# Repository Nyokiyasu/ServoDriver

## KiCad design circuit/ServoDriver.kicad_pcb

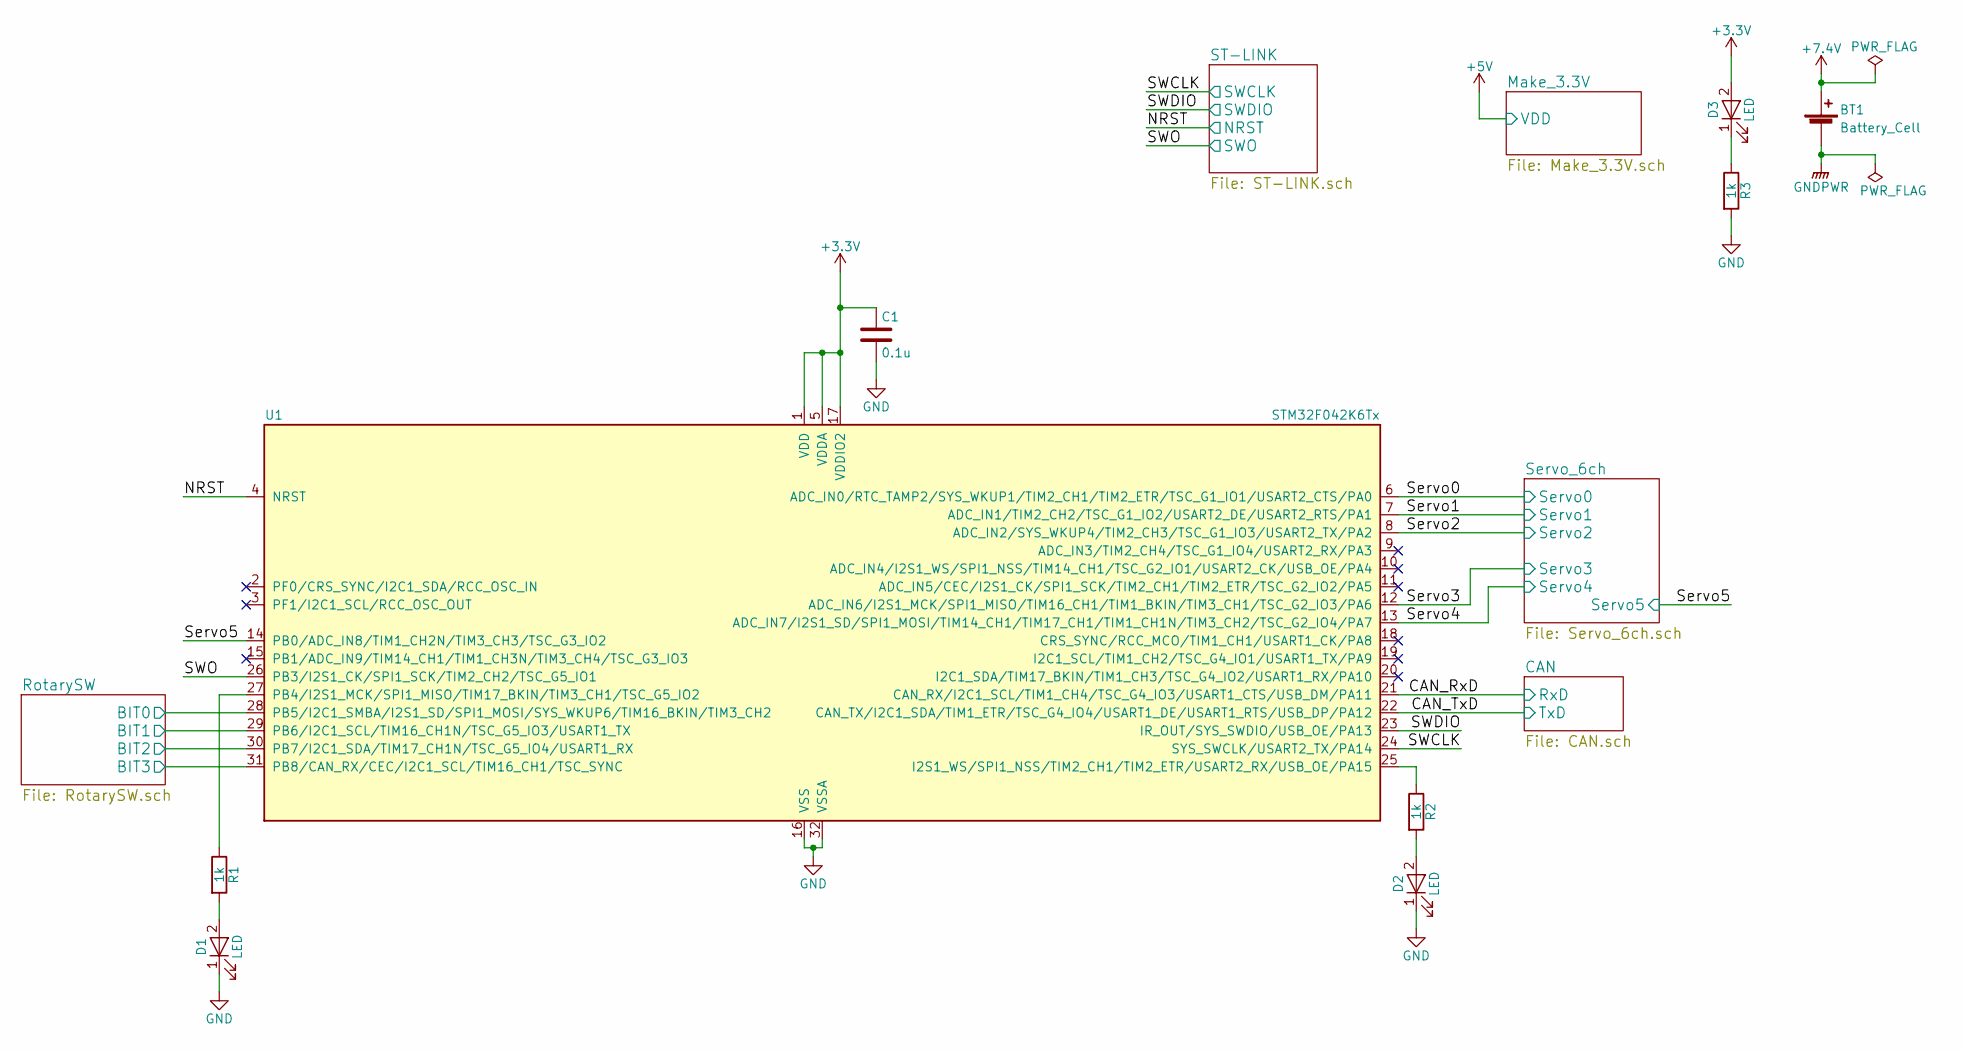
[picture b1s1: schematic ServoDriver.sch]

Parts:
BT1: Battery_Cell; XT_Mdot
C1: 0.1u; C_0603_HandSoldering
D1, D2, D3: LED; LED_D5.0mm
R1, R2, R3: 1k; R_0603_HandSoldering_LP
U1: STM32F042K6Tx; TQFP-32_7x7mm_Pitch0.8mm

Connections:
+3V3: C1.1, D3.2 (A), U1.1 (VDD), U1.5 (VDDA), U1.17 (VDDIO2); also elsewhere on the board
+7.4V: BT1.1 (+); also elsewhere on the board
/CAN_RxD: U1.21 (CAN_RX/I2C1_SCL/TIM1_CH4/TSC_G4_IO3/USA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); also elsewhere on the board
/CAN_TxD: U1.22 (CAN_TX/I2C1_SDA/TIM1_ETR/TSC_G4_IO4/USA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); also elsewhere on the board
/NRST: U1.4 (NRST); also elsewhere on the board
/RotarySW/BIT0: U1.28 (PB5/I2C1_SMBA/I2S1_SD/SPI1_MOSI/SYS_WKU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); also elsewhere on the board
/RotarySW/BIT1: U1.29 (PB6/I2C1_SCL/TIM16_CH1N/TSC_G5_IO3/USAR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); also elsewhere on the board
/RotarySW/BIT2: U1.30 (PB7/I2C1_SDA/TIM17_CH1N/TSC_G5_IO4/USAR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); also elsewhere on the board
/RotarySW/BIT3: U1.31 (PB8/CAN_RX/CEC/I2C1_SCL/TIM16_CH1/TSC_S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); also elsewhere on the board
/SWCLK: U1.24 (SYS_SWCLK/USART2_TX/PA14); also elsewhere on the board
/SWDIO: U1.23 (IR_OUT/SYS_SWDIO/USB_OE/PA13); also elsewhere on the board
/SWO: U1.26 (PB3/I2S1_CK/SPI1_SCK/TIM2_CH2/TSC_G5_IO1); also elsewhere on the board
/Servo0: U1.6 (ADC_IN0/RTC_TAMP2/SYS_WKUP1/TIM2_CH1/TI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); also elsewhere on the board
/Servo1: U1.7 (ADC_IN1/TIM2_CH2/TSC_G1_IO2/USART2_DE/U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); also elsewhere on the board
/Servo2: U1.8 (ADC_IN2/SYS_WKUP4/TIM2_CH3/TSC_G1_IO3/U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); also elsewhere on the board
/Servo3: U1.12 (ADC_IN6/I2S1_MCK/SPI1_MISO/TIM16_CH1/TI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); also elsewhere on the board
/Servo4: U1.13 (ADC_IN7/I2S1_SD/SPI1_MOSI/TIM14_CH1/TIM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); also elsewhere on the board
/Servo5: U1.14 (PB0/ADC_IN8/TIM1_CH2N/TIM3_CH3/TSC_G3_I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); also elsewhere on the board
GND: C1.2, D1.1 (K), D2.1 (K), R3.2, U1.16 (VSS), U1.32 (VSSA); also elsewhere on the board
GNDPWR: BT1.2 (-); also elsewhere on the board
unnamed: D1.2 (A), R1.2
unnamed: D2.2 (A), R2.2
unnamed: D3.1 (K), R3.1
unnamed: R1.1, U1.27 (PB4/I2S1_MCK/SPI1_MISO/TIM17_BKIN/TIM3_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)
unnamed: R2.1, U1.25 (I2S1_WS/SPI1_NSS/TIM2_CH1/TIM2_ETR/USAR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)

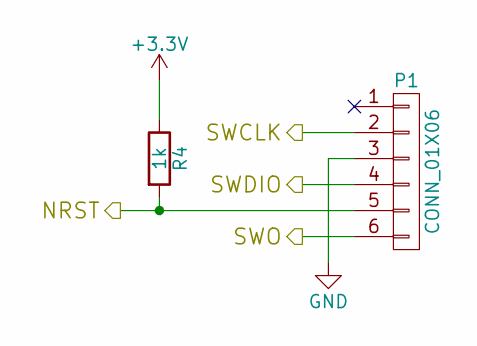
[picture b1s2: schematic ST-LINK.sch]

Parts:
P1: CONN_01X06; Pin_Header_Straight_1x06_Pitch2.54mm
R4: 1k; R_0603_HandSoldering

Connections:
+3V3: R4.1; also elsewhere on the board
/NRST: P1.5, R4.2; also elsewhere on the board
/SWCLK: P1.2; also elsewhere on the board
/SWDIO: P1.4; also elsewhere on the board
/SWO: P1.6; also elsewhere on the board
GND: P1.3; also elsewhere on the board

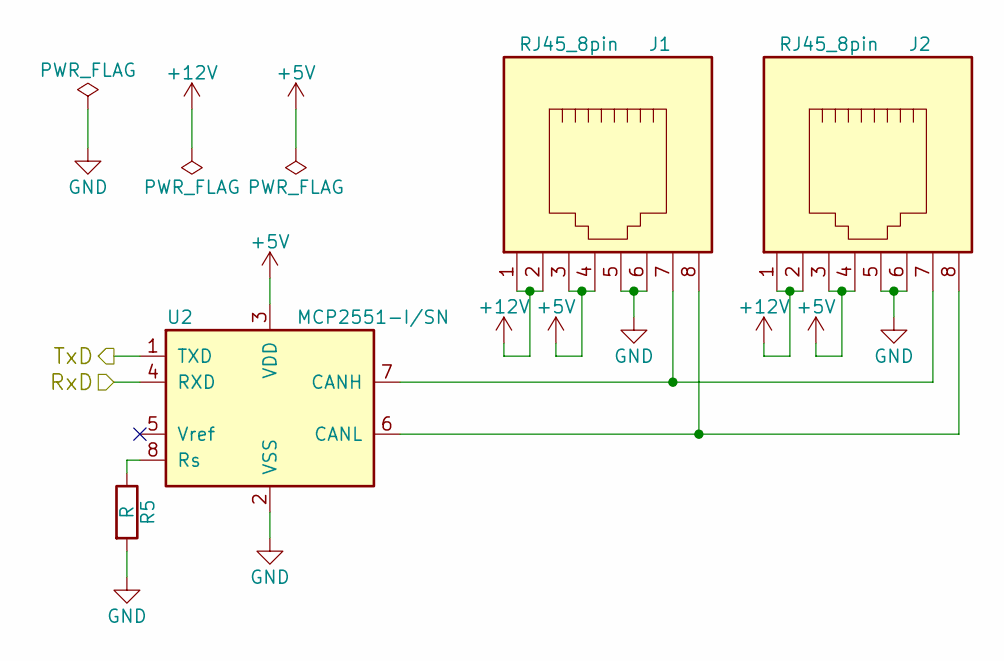
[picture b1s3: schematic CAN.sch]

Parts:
J1, J2: RJ45_8pin; 7810-8P8C
R5: R; R_0603_HandSoldering_LP
U2: MCP2551-I/SN; DIP-8_W7.62mm_Socket_LongPads

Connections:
+5V: J1.3, J1.4, J2.3, J2.4, U2.3 (VDD); also elsewhere on the board
+12V: J1.1, J1.2, J2.1, J2.2
/CAN_RxD: U2.4 (RXD); also elsewhere on the board
/CAN_TxD: U2.1 (TXD); also elsewhere on the board
GND: J1.5, J1.6, J2.5, J2.6, R5.2, U2.2 (VSS); also elsewhere on the board
unnamed: J1.7, J2.7, U2.7 (CANH)
unnamed: J1.8, J2.8, U2.6 (CANL)
unnamed: R5.1, U2.8 (Rs)

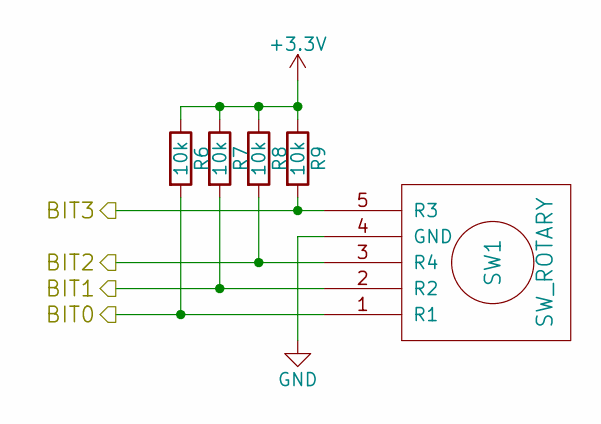
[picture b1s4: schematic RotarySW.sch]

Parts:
R6, R7, R8: 10k; R_0603_HandSoldering_LP
R9: 10k; R_Axial_DIN0207_L6.3mm_D2.5mm_P7.62mm_Horizontal
SW1: SW_ROTARY; RotarySW

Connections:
+3V3: R6.1, R7.1, R8.1, R9.1; also elsewhere on the board
/RotarySW/BIT0: R6.2, SW1.1 (R1); also elsewhere on the board
/RotarySW/BIT1: R7.2, SW1.2 (R2); also elsewhere on the board
/RotarySW/BIT2: R8.2, SW1.3 (R4); also elsewhere on the board
/RotarySW/BIT3: R9.2, SW1.5 (R3); also elsewhere on the board
GND: SW1.4 (GND); also elsewhere on the board

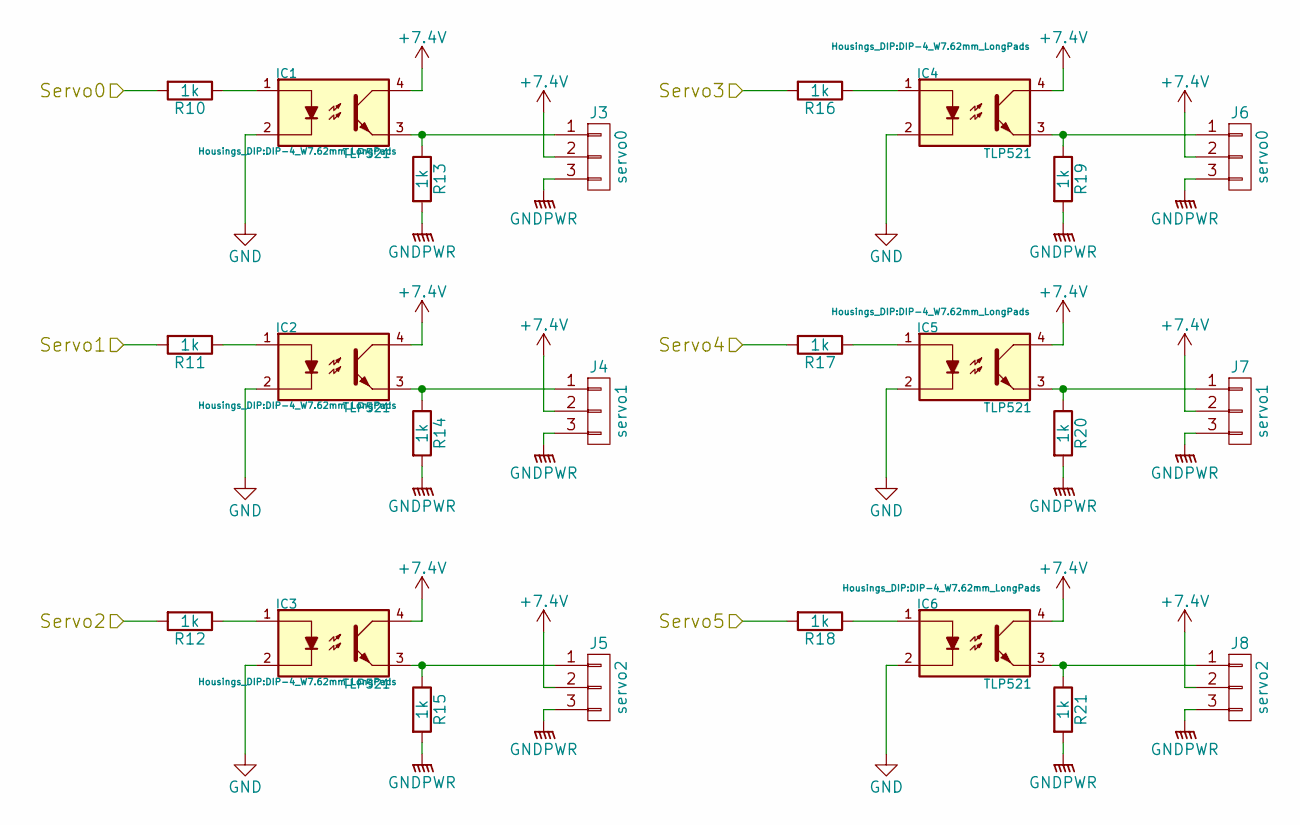
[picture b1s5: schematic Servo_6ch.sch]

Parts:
IC1, IC2, IC3, IC4, IC5, IC6: TLP521; DIP-4_W7.62mm_LongPads
J3, J6: servo0; XA_3Pin_LP
J4, J7: servo1; XA_3Pin_LP
J5, J8: servo2; XA_3Pin_LP
R10, R11, R12, R16, R17, R18: 1k; R_0603_HandSoldering
R13, R14, R15, R19, R20, R21: 1k; R_Axial_DIN0207_L6.3mm_D2.5mm_P7.62mm_Horizontal

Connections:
+7.4V: IC1.4, IC2.4, IC3.4, IC4.4, IC5.4, IC6.4, J3.2, J4.2, J5.2, J6.2, J7.2, J8.2; also elsewhere on the board
/Servo0: R10.2; also elsewhere on the board
/Servo1: R11.2; also elsewhere on the board
/Servo2: R12.2; also elsewhere on the board
/Servo3: R16.2; also elsewhere on the board
/Servo4: R17.2; also elsewhere on the board
/Servo5: R18.2; also elsewhere on the board
GND: IC1.2, IC2.2, IC3.2, IC4.2, IC5.2, IC6.2; also elsewhere on the board
GNDPWR: J3.3, J4.3, J5.3, J6.3, J7.3, J8.3, R13.2, R14.2, R15.2, R19.2, R20.2, R21.2; also elsewhere on the board
unnamed: IC1.1, R10.1
unnamed: IC1.3, J3.1, R13.1
unnamed: IC2.1, R11.1
unnamed: IC2.3, J4.1, R14.1
unnamed: IC3.1, R12.1
unnamed: IC3.3, J5.1, R15.1
unnamed: IC4.1, R16.1
unnamed: IC4.3, J6.1, R19.1
unnamed: IC5.1, R17.1
unnamed: IC5.3, J7.1, R20.1
unnamed: IC6.1, R18.1
unnamed: IC6.3, J8.1, R21.1

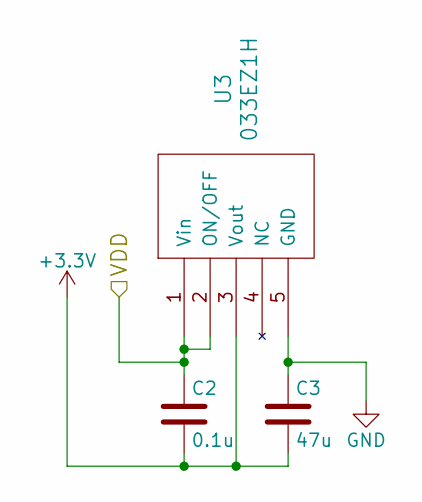
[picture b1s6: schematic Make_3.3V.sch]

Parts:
C2: 0.1u; C_0805_HandSoldering
C3: 47u; C_1210_HandSoldering
U3: 033EZ1H; PQ033EZ1HZ

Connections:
+3V3: C2.2, C3.2, U3.3 (Vout); also elsewhere on the board
+5V: C2.1, U3.1 (Vin), U3.2 (ON/OFF); also elsewhere on the board
GND: C3.1, U3.5 (GND); also elsewhere on the board

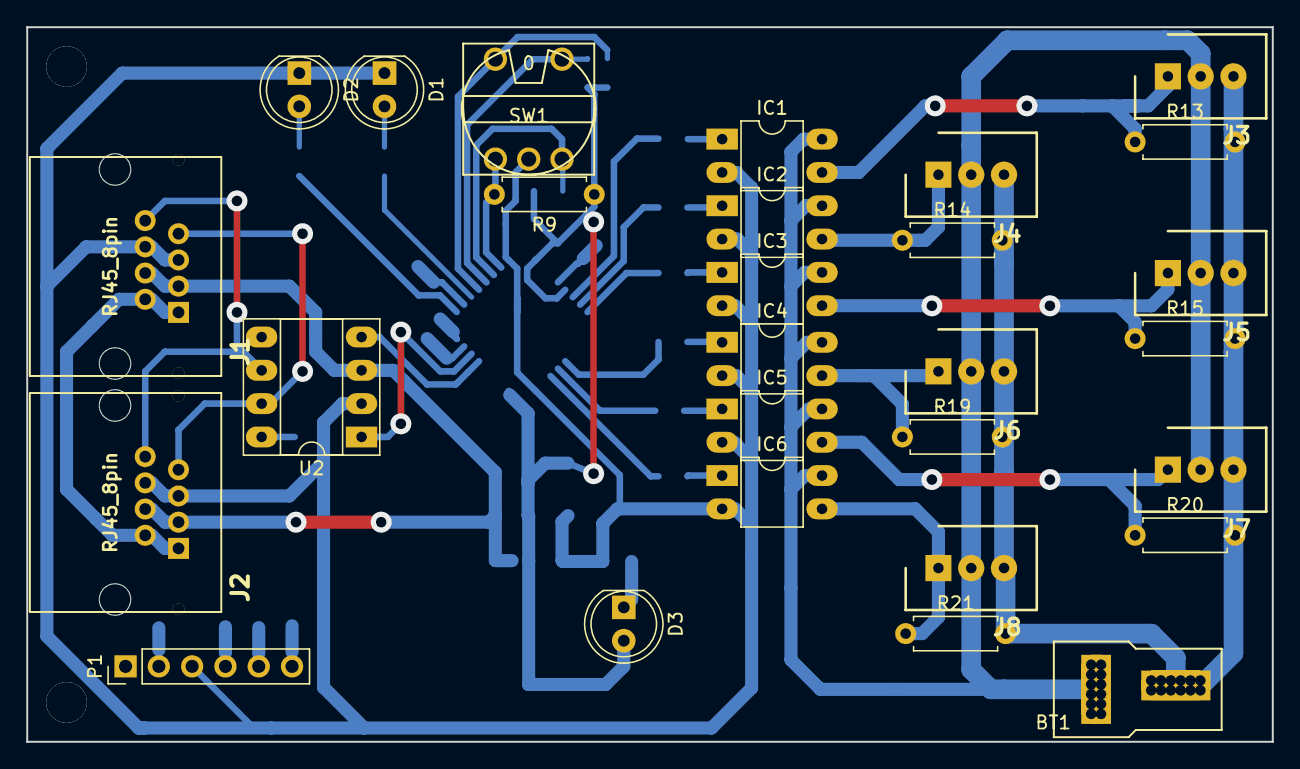
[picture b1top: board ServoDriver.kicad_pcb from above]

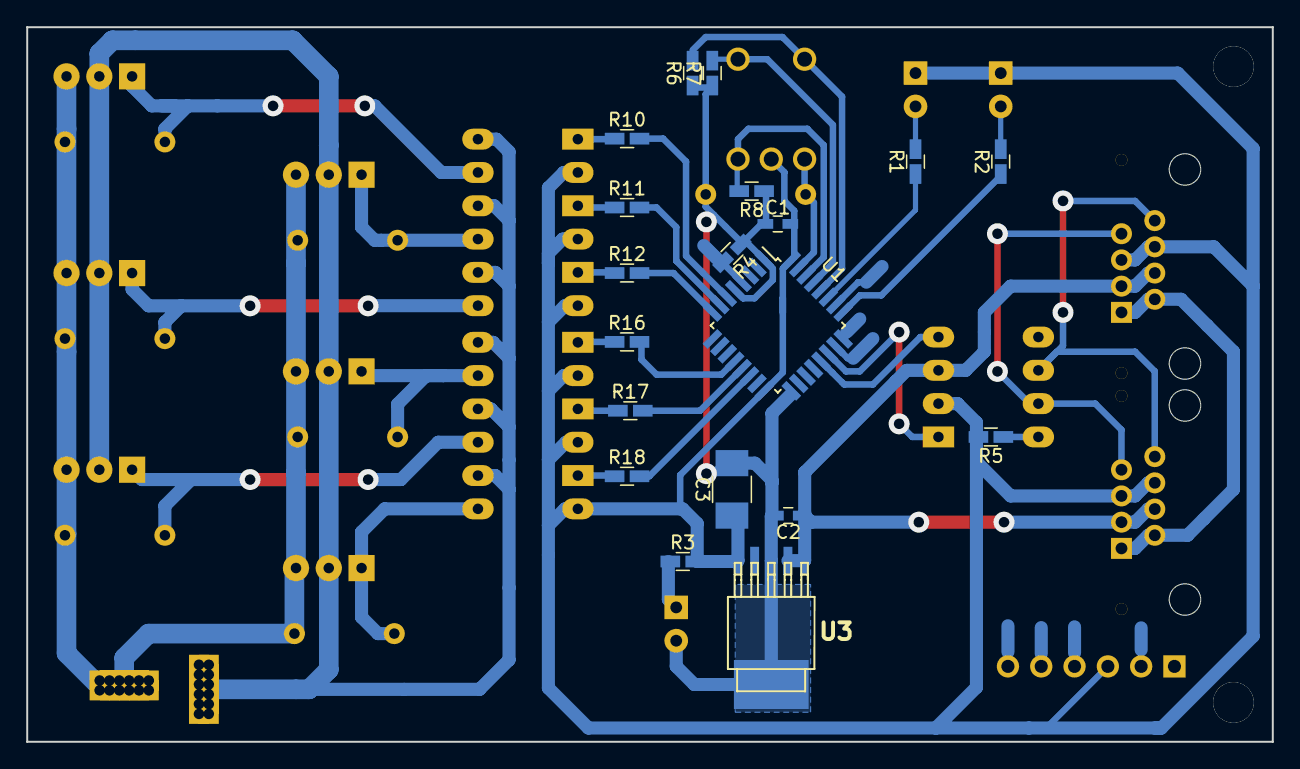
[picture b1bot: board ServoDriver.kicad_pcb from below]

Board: 2 copper layers, 95.0 x 54.5 mm, 47 parts (19 on the bottom side), 42 nets.

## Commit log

2017-06-22 書き始め
2017-06-24 CAN部分の書き足し
2017-06-28 変更点忘れた
2017-06-29 サーボの制御信号絶縁とシート分け
2017-06-29 階層ピンの追加
2017-07-21 Servoのchを4->6に変更
2017-07-21 回路図と部品表完了
2017-07-22 実態配線図の部品配置を大まかに決定
2017-07-22 抵抗の大きさを変更
2017-07-23 モータ側の配線完了
2017-07-23 コアを斜めにした
2017-07-23 基板外形線の追加
2017-07-23 ロータリースイッチとLEDのピンを変更
2017-07-23 ロータリースイッチの配線終わり
2017-07-24 レギュレータまわりの配線完了
2017-07-25 配線完了
2017-07-25 SWDのところにパッドを追加
2017-07-25 プログラムの作成
2017-07-25 RotarySWとLEDの初期化を追加
2017-07-25 New files
2017-07-28 基板加工用にデータを変更したやつを追加
2017-07-29 ファイル構造の変更
2017-07-29 関数枠作製
2017-07-29 timerのとこ書き始め
2017-07-30 timer3の初期化を追加
2017-07-30 サーボのドライブ関数を作成
2017-07-31 デバッグ用の記述
2017-07-31 Init追加
2017-07-31 ミス修正
2017-07-31 filterinit receive追加
2017-07-31 チップ抵抗の大きさ変更とガーバー出力のための手直し
2017-07-31 レギュレータのところがベタになってなかったから直した
2017-08-02 スタートアップに割り込み関数の記述とデバッグ
2017-08-04 出力のデバッグ完了,Timerの初期化関数を一部変更
2017-08-04 CANの初期化が間違っていたので修正
